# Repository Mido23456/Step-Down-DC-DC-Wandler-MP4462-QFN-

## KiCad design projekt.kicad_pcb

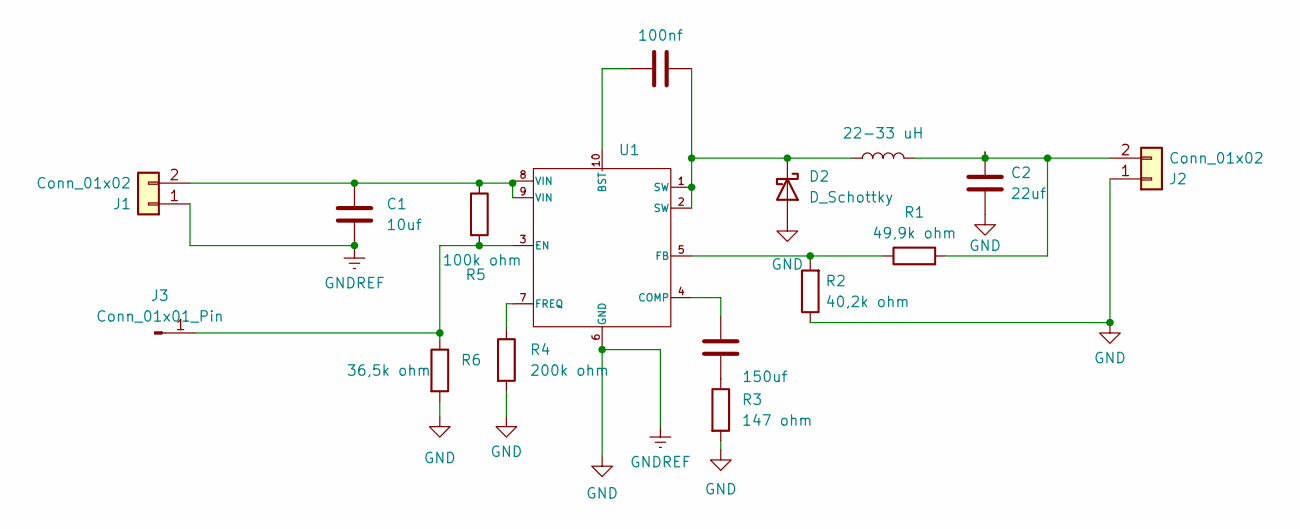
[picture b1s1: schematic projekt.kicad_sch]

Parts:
C1: 10uf; C_0805_2012Metric
C2: 22uf; C_0805_2012Metric
C3: 150uf; C_0805_2012Metric
C4: 100nf; C_0603_1608Metric
D2: D_Schottky; D_0805_2012Metric
J1, J2: Conn_01x02; PhoenixContact_MCV_1,5_2-G-3.5_1x02_P3.50mm_Vertical
J3: Conn_01x01_Pin; Pin_D0.7mm_L6.5mm_W1.8mm_FlatFork
L1: 22-33 uH; L_1206_3216Metric
R1: 49,9k ohm; R_0603_1608Metric
R2: 40,2k ohm; R_0603_1608Metric
R3: 147 ohm; R_0603_1608Metric
R4: 200k ohm; R_0603_1608Metric
R5: 100k ohm; R_0603_1608Metric
R6: 36,5k ohm; R_0603_1608Metric
U1: DFN-10_2x2mm_P0.4mm

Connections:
GND: C1.2, C2.2, D2.2 (A), J1.1, J2.1, R2.1, R3.2, R4.2, R6.2, U1.6 (GND)
unnamed: C3.2, R3.1
unnamed: C4.1, D2.1 (K), L1.1, U1.1 (SW), U1.2 (SW)
unnamed: C1.1, J1.2, R5.1, U1.8 (VIN), U1.9 (VIN)
unnamed: C2.1, J2.2, L1.2, R1.2
unnamed: J3.1, R5.2, R6.1, U1.3 (EN)
unnamed: C4.2, U1.10 (BST)
unnamed: C3.1, U1.4 (COMP)
unnamed: R1.1, R2.2, U1.5 (FB)
unnamed: R4.1, U1.7 (FREQ)

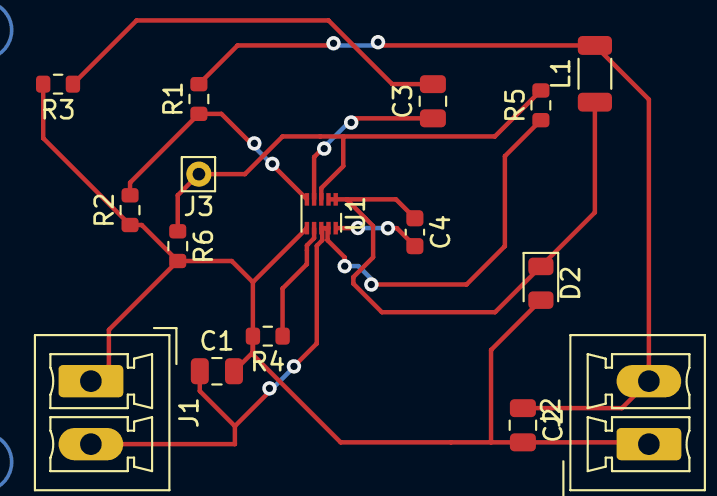
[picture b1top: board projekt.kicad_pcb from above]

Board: 2 copper layers, 16 parts (0 on the bottom side), 10 nets.
